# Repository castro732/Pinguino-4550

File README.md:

#Pingüino 4550

## Description

Board for a Pingüino with a PIC 18F4550.

##Features
- USB type B input.
- Jumper selector for power supply (USB or External).
	- External input provides a PowerJack or a Screw Terminal.
	- External input must be between 7V and 12V.
- ICSP input for programming directly to the PIC using a PICKit2 (useful for uploading the bootloader).
- Reset button.
- Power and User LEDs.
- Mounting holes.
- Small form factor, ~9cm x ~6cm

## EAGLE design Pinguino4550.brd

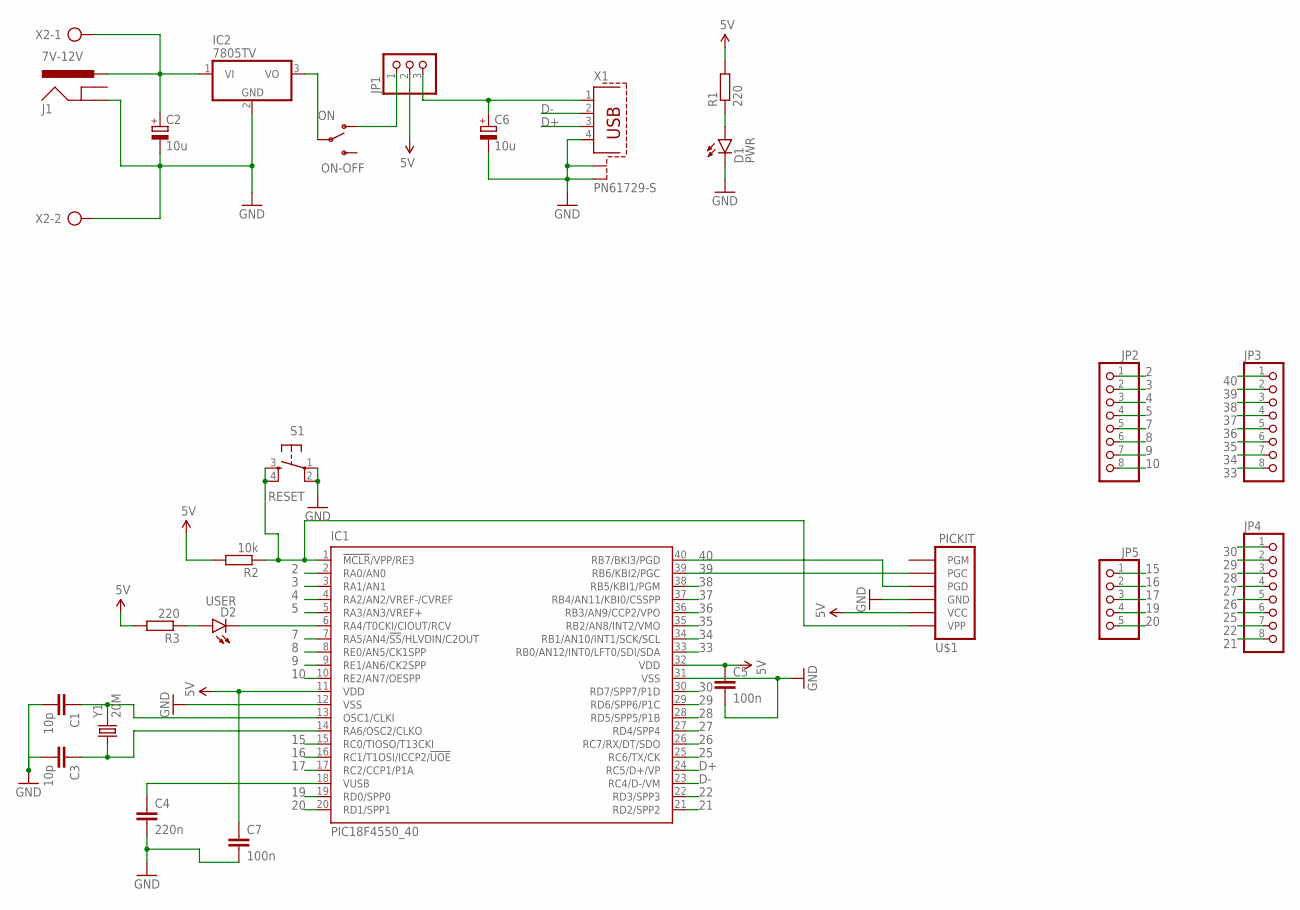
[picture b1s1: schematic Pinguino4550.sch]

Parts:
C1, C3: 10p; C025-030X050
C2, C6: 10u; E2,5-5
C4: 220n; C025-030X050
C5, C7: 100n; C025-030X050
D1: PWR; LED5MM
D2: USER; LED5MM
IC1: PIC18F4550_40; DIL40
IC2: 7805TV; TO220V
J1: 7V-12V; POWER_JACK_SLOT
JP1: PINHD-1X3; 1X03
JP2, JP3, JP4: PINHD-1X8; 1X08
JP5: PINHD-1X5; 1X05
ON-OFF: ON; SWITCH-SPDT
R1, R3: 220; 0207/7
R2: 10k; 0207/7
S1: RESET; TACTILE-PTH
U$1: PICKIT; MOLEX-1X6_LOCK
X1: PN61729-S
X2: AK500/2
Y1: 20M; HC49US

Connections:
2: IC1.2 (RA0/AN0), JP2.1
3: IC1.3 (RA1/AN1), JP2.2
4: IC1.4 (RA2/AN2/VREF-/CVREF), JP2.3
5: IC1.5 (RA3/AN3/VREF+), JP2.4
5V: C5.1, C7.1, IC1.11 (VDD), IC1.32 (VDD), JP1.2, R1.2, R2.2, R3.2, U$1.5 (VCC)
7: IC1.7 (RA5/AN4/!SS!/HLVDIN/C2OUT), JP2.5
8: IC1.8 (RE0/AN5/CK1SPP), JP2.6
9: IC1.9 (RE1/AN6/CK2SPP), JP2.7
10: IC1.10 (RE2/AN7/OESPP), JP2.8
15: IC1.15 (RC0/TIOSO/T13CKI), JP5.1
16: IC1.16 (RC1/T1OSI/ICCP2/!UOE), JP5.2
17: IC1.17 (RC2/CCP1/P1A), JP5.3
19: IC1.19 (RD0/SPP0), JP5.4
20: IC1.20 (RD1/SPP1), JP5.5
21: IC1.21 (RD2/SPP2), JP4.8
22: IC1.22 (RD3/SPP3), JP4.7
25: IC1.25 (RC6/TX/CK), JP4.6
26: IC1.26 (RC7/RX/DT/SDO), JP4.5
27: IC1.27 (RD4/SPP4), JP4.4
28: IC1.28 (RD5/SPP5/P1B), JP4.3
29: IC1.29 (RD6/SPP6/P1C), JP4.2
30: IC1.30 (RD7/SPP7/P1D), JP4.1
33: IC1.33 (RB0/AN12/INT0/LFT0/SDI/SDA), JP3.8
34: IC1.34 (RB1/AN10/INT1/SCK/SCL), JP3.7
35: IC1.35 (RB2/AN8/INT2/VMO), JP3.6
36: IC1.36 (RB3/AN9/CCP2/VPO), JP3.5
37: IC1.37 (RB4/AN11/KBI0/CSSPP), JP3.4
38: IC1.38 (RB5/KBI1/PGM), JP3.3
39: IC1.39 (RB6/KBI2/PGC), JP3.2, U$1.2 (PGC)
40: IC1.40 (RB7/BKI3/PGD), JP3.1, U$1.3 (PGD)
D+: IC1.24 (RC5/D+/VP), X1.3
D-: IC1.23 (RC4/D-/VM), X1.2
GND: C1.2, C2.-, C3.2, C4.2, C5.2, C6.-, C7.2, D1.K (C), IC1.12 (VSS), IC1.31 (VSS), IC2.2 (GND), J1.GND@2 (GND), S1.1, S1.2, U$1.4 (GND), X1.4, X1.S1, X1.S2, X2.2
unnamed: C2.+, IC2.1 (VI), J1.PWR, X2.1
unnamed: D1.A, R1.1
unnamed: IC2.3 (VO), ON-OFF.2
unnamed: JP1.1, ON-OFF.1 (O)
unnamed: C1.1, IC1.13 (OSC1/CLKI), Y1.2
unnamed: C6.+, JP1.3, X1.1
unnamed: C3.1, IC1.14 (RA6/OSC2/CLKO), Y1.1
unnamed: IC1.1 (!MCLR!/VPP/RE3), R2.1, S1.3, S1.4, U$1.6 (VPP)
unnamed: D2.K (C), IC1.6 (RA4/T0CKI/CIOUT/RCV)
unnamed: D2.A, R3.1
unnamed: C4.1, IC1.18 (VUSB)

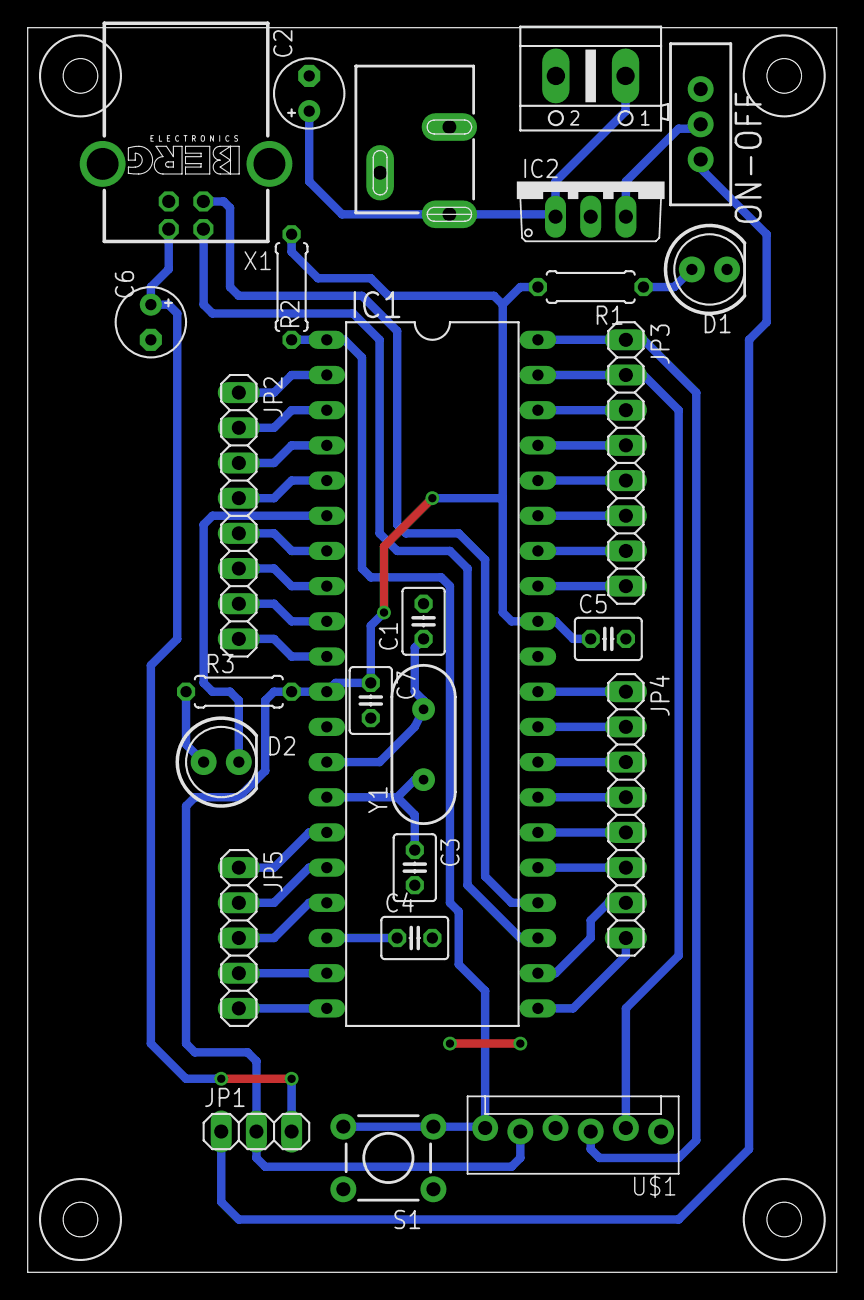
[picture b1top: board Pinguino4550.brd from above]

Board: 2 copper layers, 58.4 x 89.8 mm, 30 parts (0 on the bottom side), 44 nets.

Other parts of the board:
U$2, U$4, U$5, U$6: DRIL-2,5

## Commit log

2016-08-06 Add files

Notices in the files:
parts and their libraries:
SparkFun-LED: Licensing: Creative Commons ShareAlike 4.0 International - https://creativecommons.org/licenses/by-sa/4.0
